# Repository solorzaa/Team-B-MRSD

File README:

Fieldroid is your autonomous field painting solution.

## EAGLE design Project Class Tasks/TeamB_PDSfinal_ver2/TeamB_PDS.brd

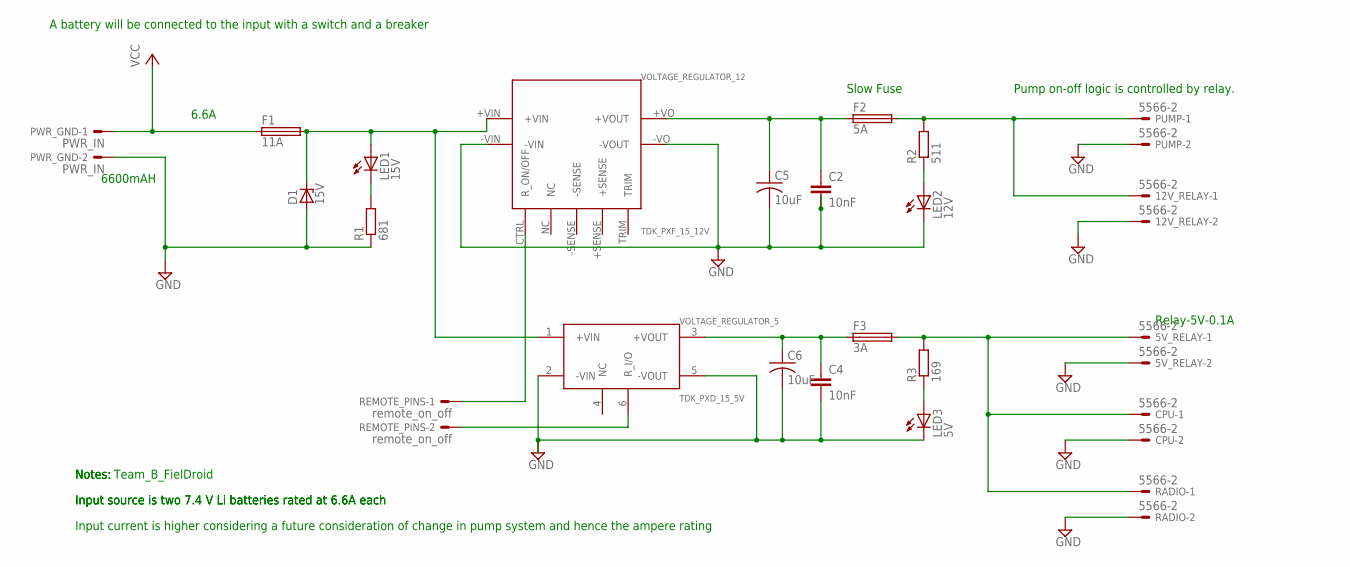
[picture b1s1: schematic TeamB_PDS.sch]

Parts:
5V_RELAY, 12V_RELAY: 5566-2
C2, C4: 10nF; C2.5-4
C5, C6: 10uF; C050-024X044
CPU: 5566-2
D1: 15V; ZDIO-5
F1: 11A; SH25
F2: 5A; SH25
F3: 3A; SH25
LED1: 15V; LED5MM
LED2: 12V; LED5MM
LED3: 5V; LED5MM
PUMP: 5566-2
PWR_GND: PWR_IN; 5566-2
R1: 681; 0204/7
R2: 511; 0204/7
R3: 169; 0204/7
RADIO: 5566-2
REMOTE_PINS: remote_on_off; 5566-2
VOLTAGE_REGULATOR_5: TDK_PXD_15_5V; TDK-PXD_15-5V
VOLTAGE_REGULATOR_12: TDK_PXF_15_12V

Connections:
GND: 5V_RELAY.2, 12V_RELAY.2, C2.2, C4.2, C5.2, C6.2, CPU.2, D1.A, LED2.K (C), LED3.K (C), PUMP.2, PWR_GND.2, R1.1, RADIO.2, VOLTAGE_REGULATOR_5.2 (-VIN), VOLTAGE_REGULATOR_5.5 (-VOUT), VOLTAGE_REGULATOR_12.-VIN, VOLTAGE_REGULATOR_12.-VO (-VOUT)
unnamed: D1.C, F1.2, LED1.A, VOLTAGE_REGULATOR_5.1 (+VIN), VOLTAGE_REGULATOR_12.+VIN
unnamed: LED1.K (C), R1.2
unnamed: C2.1, C5.1, F2.1, VOLTAGE_REGULATOR_12.+VO (+VOUT)
unnamed: 12V_RELAY.1, F2.2, PUMP.1, R2.2
unnamed: LED2.A, R2.1
unnamed: REMOTE_PINS.1, VOLTAGE_REGULATOR_12.CTRL (R_ON/OFF)
unnamed: REMOTE_PINS.2, VOLTAGE_REGULATOR_5.6 (R_I/O)
unnamed: C4.1, C6.1, F3.1, VOLTAGE_REGULATOR_5.3 (+VOUT)
unnamed: 5V_RELAY.1, CPU.1, F3.2, R3.2, RADIO.1
unnamed: LED3.A, R3.1
VCC: F1.1, PWR_GND.1

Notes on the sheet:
Pump on-off logic is controlled by relay.
Input current is higher considering a future consideration of change in pump system and hence the ampere rating
Input source is two 7.4 V Li batteries rated at 6.6A each
Notes:
Team_B_FielDroid
6600mAH
A battery will be connected to the input with a switch and a breaker
Slow Fuse
6.6A
Relay-5V-0.1A

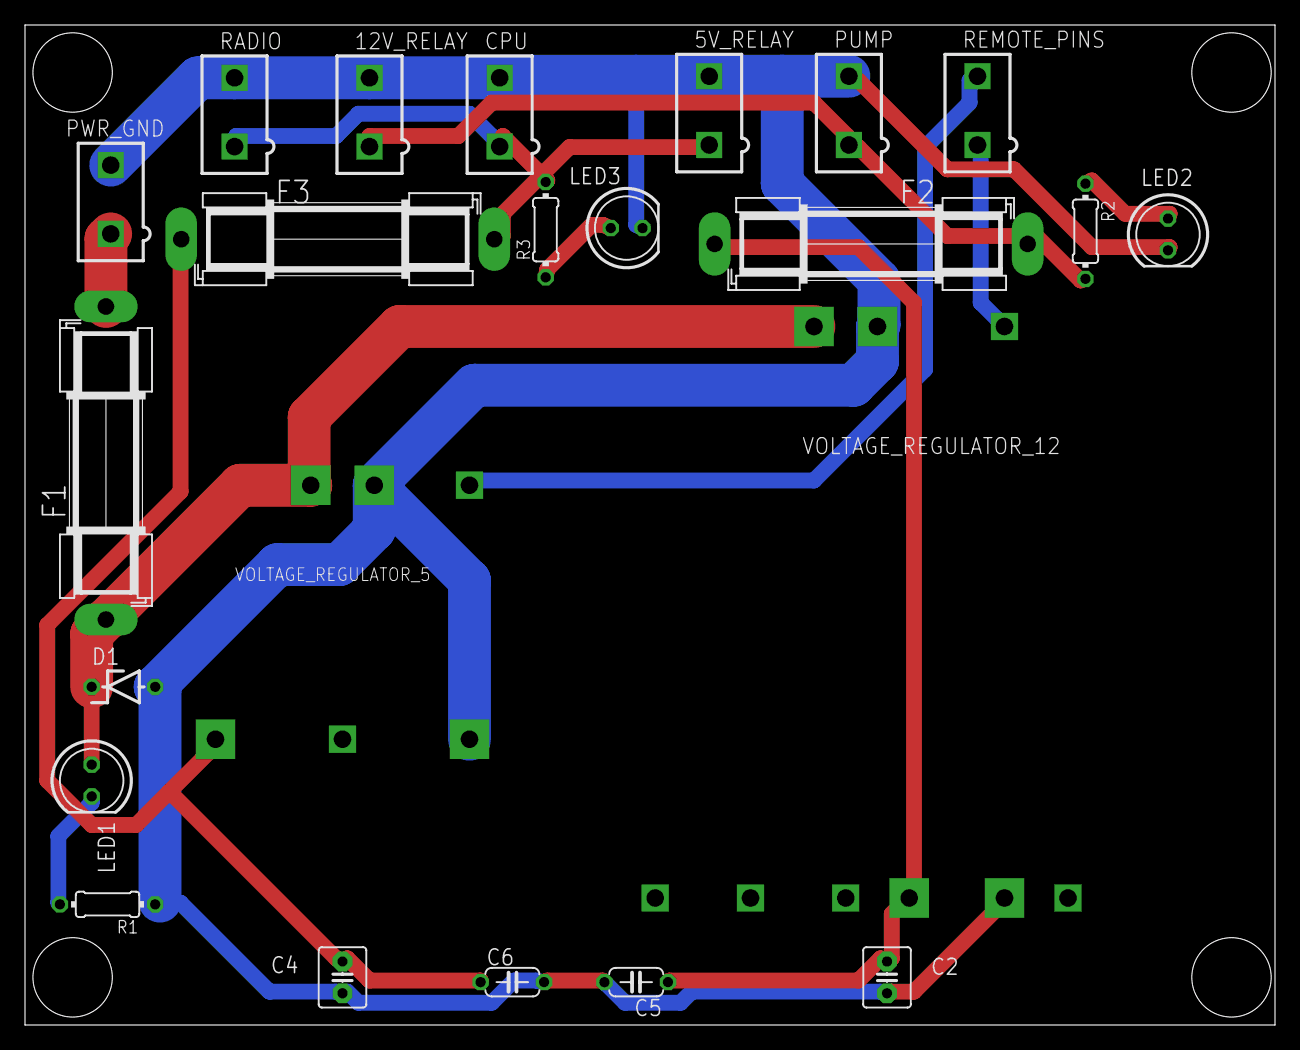
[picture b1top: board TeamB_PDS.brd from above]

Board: 2 copper layers, 100.0 x 80.0 mm, 23 parts (0 on the bottom side), 12 nets.

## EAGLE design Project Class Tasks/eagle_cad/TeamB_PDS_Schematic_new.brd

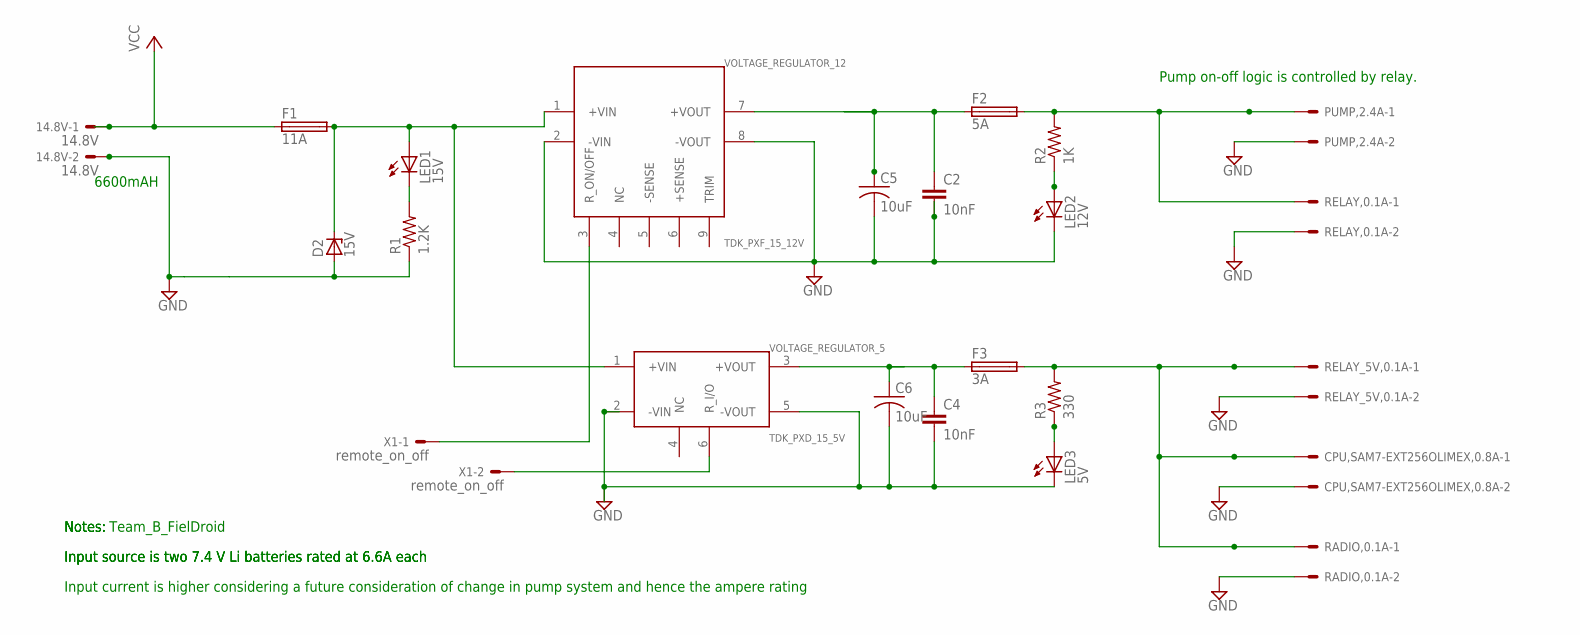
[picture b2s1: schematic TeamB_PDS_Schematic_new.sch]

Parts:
14.8V: 14.8V; 5566-2
C2, C4: 10nF; C2.5-4
C5, C6: 10uF; C050-045X075
CPU,SAM7-EXT256OLIMEX,0.8A: 5566-2
D2: 15V; DO41Z10
F1: 11A; FUSE_HOLDER_5X20MM
F2: 5A; FUSE_HOLDER_5X20MM
F3: 3A; FUSE_HOLDER_5X20MM
LED1: 15V; LED5MM
LED2: 12V; LED5MM
LED3: 5V; LED5MM
PUMP,2.4A: 5566-2
R1: 1.2K; 0309/12
R2: 1K; 0309/12
R3: 330; 0309/12
RADIO,0.1A: 5566-2
RELAY,0.1A: 5566-2
RELAY_5V,0.1A: 5566-2
VOLTAGE_REGULATOR_5: TDK_PXD_15_5V; TDK-PXD_15-5V
VOLTAGE_REGULATOR_12: TDK_PXF_15_12V
X1: remote_on_off; 5566-2

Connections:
GND: 14.8V.2, C2.2, C4.2, C5.2, C6.2, CPU,SAM7-EXT256OLIMEX,0.8A.2, D2.A, LED2.K (C), LED3.K (C), PUMP,2.4A.2, R1.1, RADIO,0.1A.2, RELAY,0.1A.2, RELAY_5V,0.1A.2, VOLTAGE_REGULATOR_5.2 (-VIN), VOLTAGE_REGULATOR_5.5 (-VOUT), VOLTAGE_REGULATOR_12.2 (-VIN), VOLTAGE_REGULATOR_12.8 (-VOUT)
unnamed: LED1.K (C), R1.2
unnamed: C4.1, C6.1, F3.1, VOLTAGE_REGULATOR_5.3 (+VOUT)
unnamed: D2.C, F1.2, LED1.A, VOLTAGE_REGULATOR_5.1 (+VIN), VOLTAGE_REGULATOR_12.1 (+VIN)
unnamed: C2.1, C5.1, F2.1, VOLTAGE_REGULATOR_12.7 (+VOUT)
unnamed: LED2.A, R2.1
unnamed: VOLTAGE_REGULATOR_12.3 (R_ON/OFF), X1.1
unnamed: VOLTAGE_REGULATOR_5.6 (R_I/O), X1.2
unnamed: CPU,SAM7-EXT256OLIMEX,0.8A.1, F3.2, R3.2, RADIO,0.1A.1, RELAY_5V,0.1A.1
unnamed: LED3.A, R3.1
RELAY_12V,0.1A: F2.2, PUMP,2.4A.1, R2.2, RELAY,0.1A.1
VCC,14.8V,6.6A: 14.8V.1, F1.1

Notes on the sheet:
Pump on-off logic is controlled by relay.
Input current is higher considering a future consideration of change in pump system and hence the ampere rating
Input source is two 7.4 V Li batteries rated at 6.6A each
Notes:
Team_B_FielDroid
6600mAH

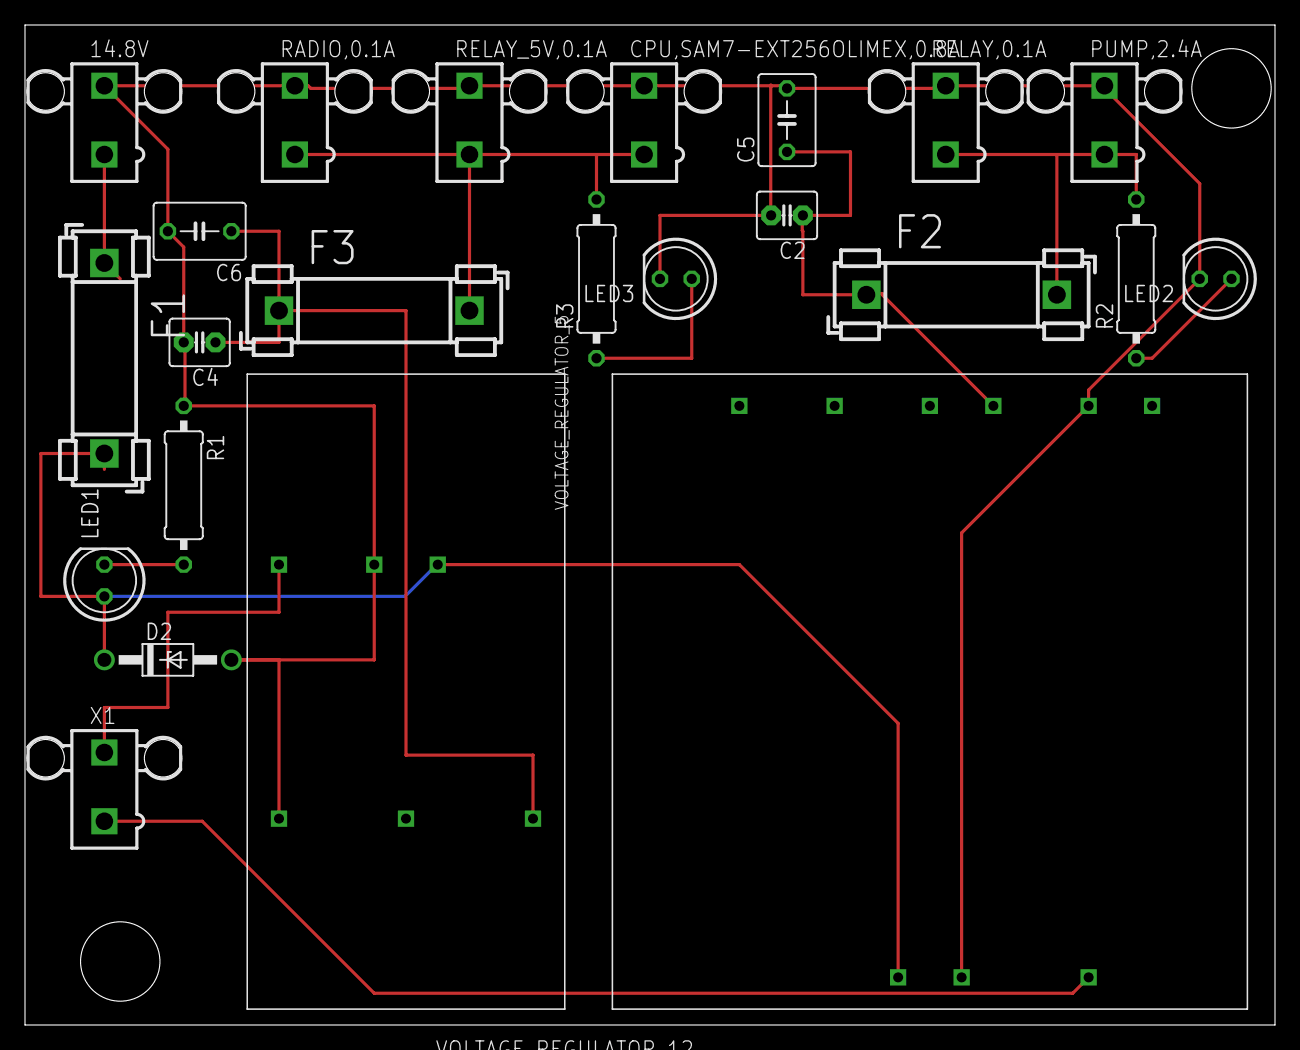
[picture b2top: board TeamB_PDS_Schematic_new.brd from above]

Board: 2 copper layers, 100.0 x 80.0 mm, 23 parts (0 on the bottom side), 12 nets.

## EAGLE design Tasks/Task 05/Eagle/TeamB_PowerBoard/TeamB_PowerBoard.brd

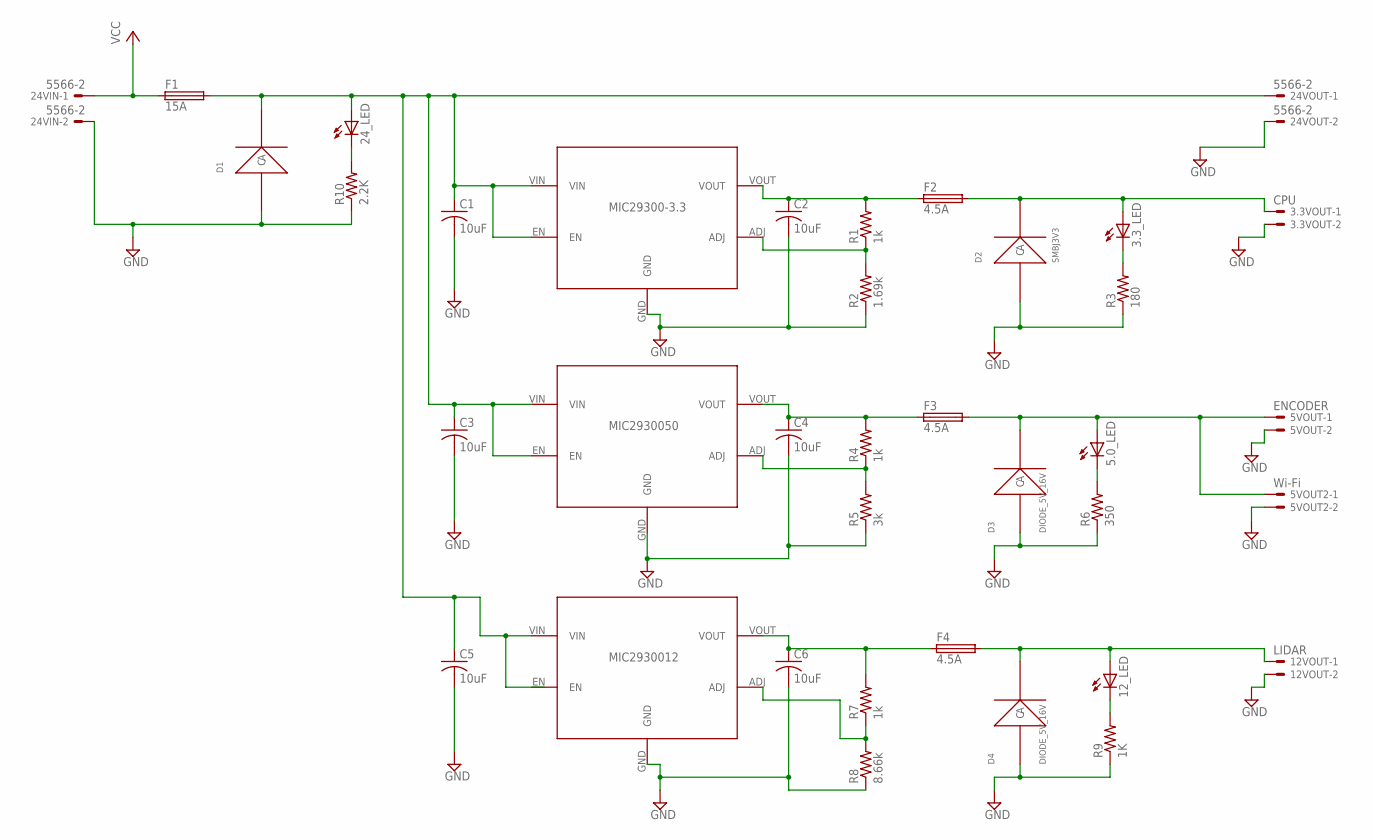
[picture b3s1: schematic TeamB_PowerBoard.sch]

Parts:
3.3VOUT: CPU; 70543-02
3.3_LED, 5.0_LED, 12_LED, 24_LED: LEDSML1206; SML1206
5VOUT: ENCODER; 70543-02
5VOUT2: Wi-Fi; 70543-02
12VOUT: LIDAR; 70543-02
24VIN, 24VOUT: 5566-2
C1, C2, C3, C4, C5, C6: 10uF; C2220K
D1: DIODE_26
D2: SMBJ3V3
D3, D4: DIODE_5V_16V
F1: 15A; TE5
F2, F3, F4: 4.5A; TE5
R1, R4, R7: 1k; R1206
R2: 1.69k; R1206
R3: 180; R1206
R5: 3k; R1206
R6: 350; R1206
R8: 8.66k; R1206
R9: 1K; R1206
R10: 2.2K; R1206
U$1, U$2, U$3: MIC29300; MIC29300WU

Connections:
GND: 3.3VOUT.2, 5VOUT.2, 5VOUT2.2, 12VOUT.2, 24VIN.2, 24VOUT.2, C1.2, C2.2, C3.2, C4.2, C5.2, C6.2, D1.1 (A), D2.1 (A), D3.1 (A), D4.1 (A), R2.1, R3.1, R5.1, R6.1, R8.1, R9.1, R10.1, U$1.GND, U$2.GND, U$3.GND
unnamed: 24VOUT.1, 24_LED.A, C1.1, C3.1, C5.1, D1.2 (C), F1.2, U$1.EN, U$1.VIN, U$2.EN, U$2.VIN, U$3.VIN
unnamed: 5.0_LED.C, R6.2
unnamed: 24_LED.C, R10.2
unnamed: 5.0_LED.A, 5VOUT.1, 5VOUT2.1, D3.2 (C), F3.2
unnamed: C2.1, F2.1, R1.2, U$1.VOUT
unnamed: 12VOUT.1, 12_LED.A, D4.2 (C), F4.2
unnamed: C4.1, F3.1, R4.2, U$2.VOUT
unnamed: C6.1, F4.1, R7.2, U$3.VOUT
unnamed: 3.3VOUT.1, 3.3_LED.A, D2.2 (C), F2.2
unnamed: 12_LED.C, R9.2
unnamed: 3.3_LED.C, R3.2
unnamed: R1.1, R2.2, U$1.ADJ
unnamed: R4.1, R5.2, U$2.ADJ
unnamed: R7.1, R8.2, U$3.ADJ
VCC: 24VIN.1, F1.1

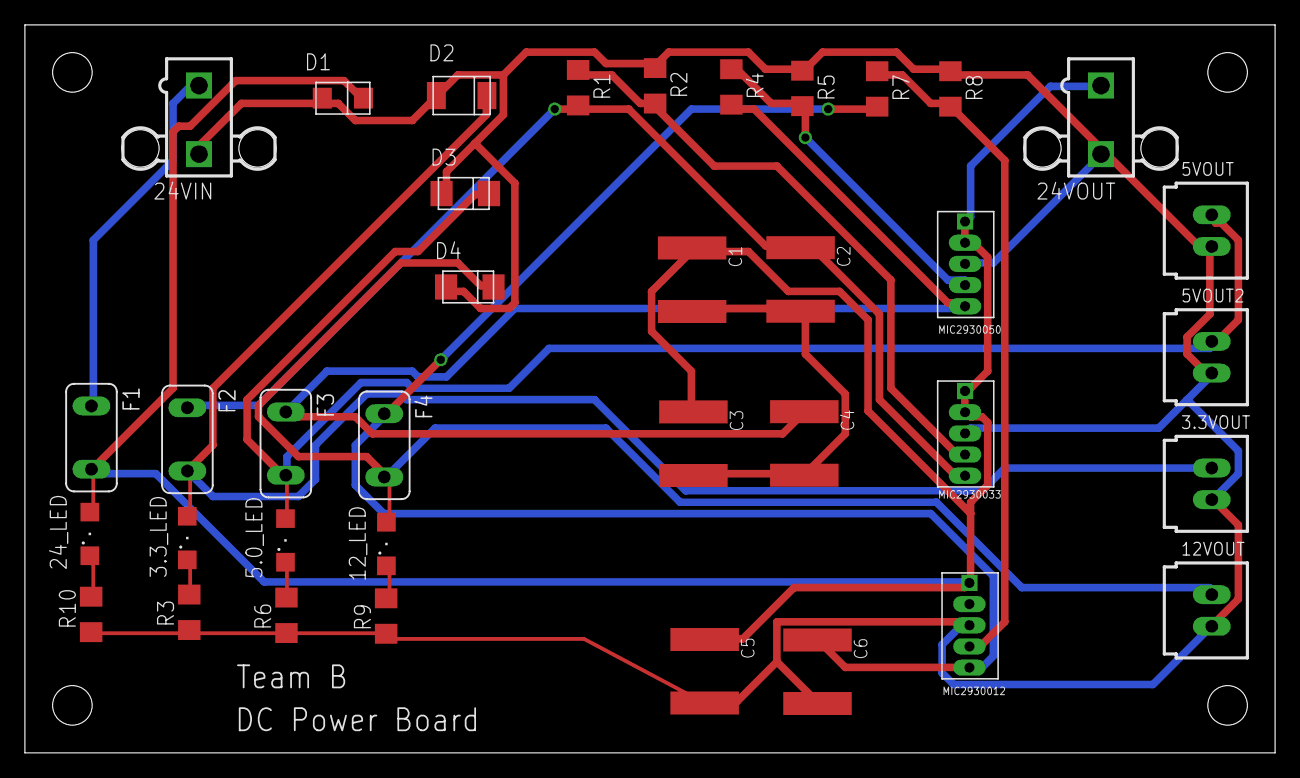
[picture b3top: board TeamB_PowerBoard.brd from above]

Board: 2 copper layers, 100.3 x 58.4 mm, 37 parts (0 on the bottom side), 16 nets.

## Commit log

2014-09-28 Added folders for Projects and tasks
2014-09-28 Added DC Converter Libs
2014-09-28 Added the Diode Library files
2014-09-28 Added Project Folder
2014-09-29 Added PCB Layout
    ERC passes for both PCB and Schematic layouts!
2014-09-29 Added the 4 holes to the PCB
2014-09-29 Saved Eagle Project Files
    Forgot to save the Eagle Project Files
2014-09-29 Added 4th LED
    Added 4th LED to PCB and Schematic
2014-09-30 Fixed Libraries and Wiring
    Fixed the Library components to reflect DIP variants.
    Fixed schematic for LED wiring.
    ERC passes for both PCB and SCH
2014-09-30 Changes to PCB layout and added 2D drawing
2014-10-03 Added submission files and cleaned up folders
2014-10-05 Adding the Gannt chart to the git. This can be checked out to make changes as we move through the semester.
2014-10-05 The readme will provide more information about this project.
2014-10-05 The contents of the website are available for review. This will help if people need to add content.
2014-10-05 Updated Gannt to 10/5 ... We're behind on Ordering CPU and drafting CAD of robot... But we are ahead on chasis construction (Thanks Stephan)
2014-10-09 CoDR Added
    Here is the submitted version of the CoDR
2014-10-09 Renamed some folders for organization
2014-10-10 The website and all its glory
2014-10-12 Added PROJECT FILES folder
    Use as WBS
2014-10-12 Added Roborun+ PC Utility and SDC2100 Firmware
2014-10-13 Added Test Plan for Localization
2014-10-15 Added Test Plan 1 for Localization
2014-10-20 Added Test Data Plan and PC Board Files
2014-10-26 Added Risk Management and CoDR with comments
2014-10-27 Added the risk managements
2014-11-01 PCB files 29th oct by jaghvi
2014-11-01 added teleop files
2014-11-01 tuned teleop motion
2014-11-03 Added Arduino Radio Files to Communication Folder
2014-11-03 Updated Gannt Chart with better deadlines and such - Will mark on physical calendar
2014-11-03 Up to date website files
2014-11-03 modified teleop.cpp
2014-11-03 deleted old .o driver programs
2014-11-04 added Power distribution files submitted for TASK11
2014-11-04 "added file git.sh"
2014-11-04 Serial python files for beaglebone to arduino (hopefully radio in near future)
2014-11-04 added serTransmit.py to transmit data via laptop to radio without the arduino
2014-11-04 modifed serTransmit file
2014-11-04 changed sample.cpp so that the bot moves in a square path
2014-11-05 square motion
2014-11-07 Modified RX/TX code
2014-11-07 added transmit file for surveygun
2014-11-08 Added e3 ecnoder datasheet
2014-11-10 Updated Gannt to 11-10-2014
2014-11-10 Put Website images on folder. Added PDR and FVE
2014-11-10 added leicaTotalStation files to Commucation System
2014-11-10 removed leicaTotalStation code
2014-11-11 " added paintsystem control code"
2014-11-14 Main Software file with commented psuedocode
2014-11-15 Made some headway on software - there are some large gaps in communicating with the drive system, no integration with IMU, and lack of loop process to iterate through points with PID - BUT! most of t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
2014-11-15 added roboteqInterface code
2014-11-16 "added python files to read data from teting survey gun"
2014-11-17 PID control updates
2014-11-17 encoderSample.o is demo for pr4
2014-11-19 added navigation.cpp for code review
2014-11-19 Rewriting the model for the drive system
2014-11-20 NAVIGATIONgit status! working...most likely
2014-11-20 PID tuning in navigation.cpp
2014-11-20 updated points file a little bit
2014-11-20 well tuned PID
2014-11-20 I NEED PIZZA
2014-11-20 I WANT PIZZA NOW
2014-11-21 additional tuning
2014-11-21 adding serReceiveNov16.cpp which is c++ file to receive radio data
2014-11-22 Changes to Risk and Index file for Website
2014-11-22 modified navigation.cpp to recieve and process Leica data
2014-11-22 Updated schedule on website
2014-11-22 Synched the website files Added FVE and PDR links
2014-11-22 Changed Website Dimensions
2014-11-22 System Implementation Stuff
2014-11-22 Updated the schedule
2014-11-22 Updated the Problem Description and added new pics
2014-11-22 Little website changes
2014-11-22 added receive file for c++
2014-11-22 Need to test accuracy of encoders
2014-11-22 Making sure we can modify distance correction to get accurate distances
2014-11-22 Testing straight lines with the leica
2014-11-22 Check error.txt for a log of what happened and navigationLineTesting was the file I was using to run the robot
2014-11-23 I think I found the tracking station frame change errors
2014-11-23 Working frames, working straight line calibration
2014-11-24 Try this file matt
2014-11-26 Matt and I are doing Machine Learning
2014-12-01 Smoother curve for path planning
2014-12-01 Adding the file with gains that I tuned for smoother and slower motion on the first path
2014-12-01 Preparing for leica tests this afternoon
2014-12-01 navigationLineTesting is the current file I'm working on
2014-12-03 The Working Code
2014-12-06 Changing the website around a bit
2014-12-06 no changes I think
2014-12-12 Gantt Update
2014-12-12 Website Updates
2015-01-15 The working code and the theta correction code
2015-01-15 Fixed name of file
2015-01-15 Made a PI with D file (added Derivative Control)
2015-01-15 Ramp Speed Torque Determiner
2015-01-15 Matt - I added torqueSpeed.cpp - this file should allow you to test the angular velocity at several torque inputs (power)
2015-01-21 added papers on MPC and differential drive control robots
2015-01-21 another paper
2015-01-23 Updated the Gantt Chart with controls additions
2015-01-23 torque speed testing?
2015-01-26 PCB 2 Board Files Added
2015-01-27 created new file for new navigation methods
2015-01-27 Made a function that creates arrays of v and w that can be adjusted for desired criteria
2015-01-28 Made 3 functions for Matt: desired path(x,y), desired path(v,w), and a projector function that projects the desired path over some given horizon
2015-01-28 class file and additional path projection functions
2015-02-01 modified newNavigiationMethod
2015-02-02 Tested Matt's Code :-D
2015-02-02 updated newNavigationMethod.cpp
2015-02-03 added functions to find optimal velocity commands to send to motors
2015-02-03 updated new functions in newNavigationMethod.cpp
2015-02-03 added file function to send wheelRPM commands in newNavigationMethod.cpp
2015-02-04 Working pieces of Matt's code
2015-02-04 testing code in tableMaker
2015-02-05 included main loop code to run MPC in newNavigationMethod.cpp
2015-02-05 quick edit
2015-02-05 Get clock time for cpu
2015-02-06 Fixed a few bugs
2015-02-06 edits and test Data files
2015-02-11 Updated Gantt Chart
2015-02-12 Full Field Lookup Goals Added
2015-02-12 Trying full field on blocks
2015-02-13 added workingMPC.cpp
2015-02-18 adding IMU files
2015-02-18 added IMU files
2015-02-19 Making Beaglebone Backup for Bluetooth Stuff
2015-02-20 added latest IMU files
2015-02-20 added consistent time functions and code for extended field into workingMPC.cpp
2015-02-21 saturdays testing code
2015-02-21 adding lates IMU files
2015-02-21 added readme for leica and tx radio comm
2015-02-21 added a readme to connect all relevant pins on bealebone
2015-02-22 IMU files
2015-02-22 added offset for IMU
2015-02-23 added code for magnetometer
2015-02-23 added the working IMU files
2015-02-23 working IMU code
2015-02-23 saturday testing code
2015-02-23 staruday's test code
2015-02-24 added lates files in srcfeb24
2015-02-24 IMU Test 1
2015-03-01 updating gantt
2015-03-02 march 1st
2015-03-02 added eigen library
2015-03-03 Redistributed Softwar to clean up file heirarchies
2015-03-03 Working code exists in progressReviewPlusIMU, last progress Review code is in progressReviewFeb, and the kalman code is in getKalmanData
2015-03-04 Adding clock syncronization code, will test tomorrow
2015-03-04 Clock Sync Update
2015-03-05 Wednesday night tests Kalman.cpp and kalmanLog files
2015-03-05 Clock Sync Updates
2015-03-05 Found a bug, fixed
2015-03-14 Added EKF code
2015-03-19 changed magnetometer files
2015-03-24 Updated the EKF to account for the leica - Model works - Robot: untested
2015-03-26 Working EKF! with leica and ecoders, needs tuning
2015-03-27 adding paint files
2015-03-27 Backed up painting code to be tested for pr11
2015-03-31 Updates for PR11
2015-03-31 Tuning the paint system
2015-04-02 PR11 Final Code
2015-04-03 features for customizing parameters
2015-04-03 edited fullFieldCustom.cpp
2015-04-05 adding case files
2015-04-06 added beaglebone ported data for magnetometer calibration
2015-04-06 changed the data file to remove the global error
2015-04-08 Corrected Field Path Integrated into System
2015-04-11 added latest IMU code
2015-04-12 added working IMu files
2015-04-13 Created Directory for SVE code
2015-04-14 everything with IMU
2015-04-14 Added ramp up velocity and fixed the path
2015-04-16 code worked then didn't
2015-04-20 Logs and such
2015-04-24 SVE Code
